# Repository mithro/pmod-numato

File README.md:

# pmod-numato

This adapter is useful for the following;

 * Adapting the "XADC" style to the "HS" style.
    - See [my high speed Pmod sheet for details](https://docs.google.com/spreadsheets/d/1D-GboyrP57VVpejQzEm0P1WEORo1LAIt92hk1bZGEoo/edit#gid=725118408).

 * From from Numato's spacing (0.3145 inch, pin to pin) to
   Digilent's spacing (0.3 inch, edge to edge).

The traces in a diff pair have been length and skewed matched with a tolerance
of ~1 mil.

The diff pairs as a group have been length matched to 0.8537 inches (21.6mm)
long with a tolerance of 20 mil (0.5mm).

To use Numato spacing device on Digilent host;
 * B side should be up.
 * The XHS side should be loaded with pins.
 * The XADC side should be loaded with socket.

To use Digilent spacing device on Numato host;
 * A side should be up.
 * The XHS side should be loaded with socket.
 * The XADC side should be loaded with pins.

# Board Manufacturing

 *  5mil (0.127mm) trace width
 *  5mil (0.127mm) trace clearance

 * 12 mil (0.3048mm) drill size
 *  6 mil (0.1524mm) annular ring
 * 24 mil (0.6096mm) via size (6mil+12mil+6mil)

 *  6 mil (0.1524) silkscreen width

This can be meet by;
 * [Hackvana by requesting the 5mil option](https://docs.google.com/document/d/1p6FH25ltGpzJQ5_8fbflDukqEKghiEcpuhJpngth2Is/edit)
 * [OHS Park's Four Layer Boards](http://docs.oshpark.com/services/)

## License

The board is licensed under a
Creative Commons Attribution-ShareAlike 4.0 International License.

You should have received a copy of the license along with this
work.  If not, see <http://creativecommons.org/licenses/by-sa/4.0/>.

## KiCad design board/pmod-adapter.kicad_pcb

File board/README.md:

5mil traces, 5mil clearance

0.8537 - length matched

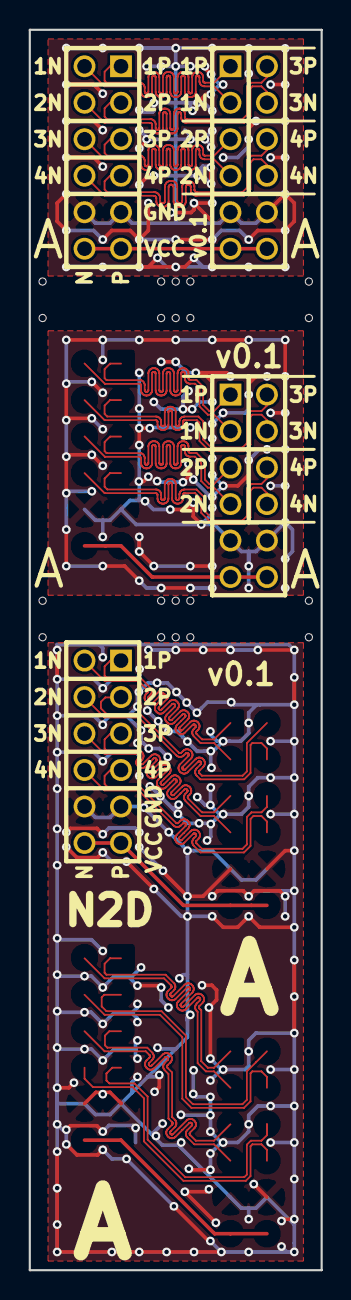
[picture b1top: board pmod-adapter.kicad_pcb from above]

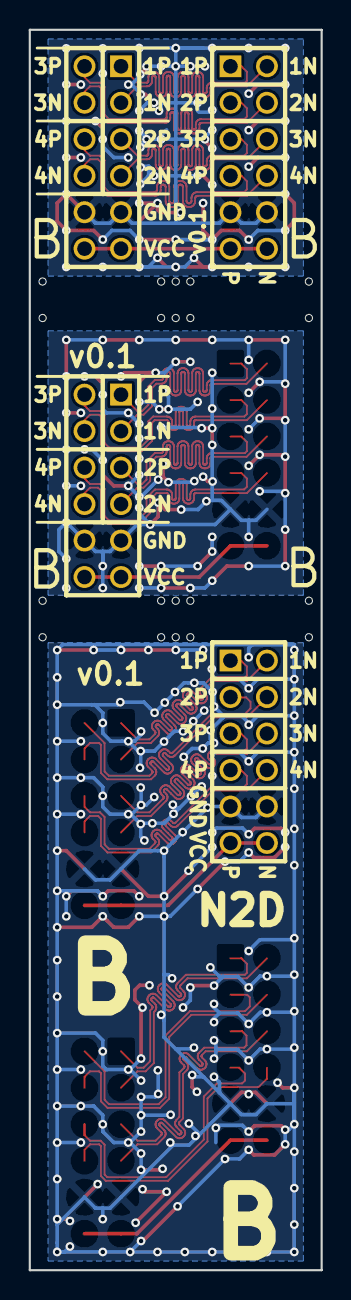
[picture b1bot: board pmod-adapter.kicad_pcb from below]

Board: 2 copper layers, 20.3 x 86.4 mm, 4 parts (2 on the bottom side), 13 nets.

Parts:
PH1, PH2: PMOD-Device-x2-Type-XHS; pmod_pin_array_6x2_hs
PX1, PX3: PMOD-Device-x2-Type-XADC; pmod_pin_array_6x2_xadc

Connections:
/GND2: PX1.5, PX1.11
/GND34: PH1.5, PH1.11, PH2.5, PH2.11, PX3.5, PX3.11
/J4A_N: PH1.2, PX3.7
/J4A_P: PH1.1, PX3.1
/J4B_N: PH1.8, PX3.8
/J4B_P: PH1.7, PX3.2
/J4C_N: PH1.4, PX3.9
/J4C_P: PH1.3, PX3.3
/J4D_N: PH1.10, PX3.10
/J4D_P: PH1.9, PX3.4
/VCC2: PX1.6, PX1.12
/VCC3: PH2.6, PH2.12
/VCC4: PH1.6, PH1.12, PX3.6, PX3.12

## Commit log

2016-11-15 Start.
2016-11-15 Adding LICENSE info.
2016-11-15 Adding another dimension.
2016-11-15 Changing the README a little.
2016-11-15 Increasing to 4 headers.
2016-11-19 Split the GND net for each part.
2016-11-19 Updating PCB.
2016-11-19 Lots of updates.
2016-11-19 Small updates.
2016-11-19 Working on getting the Numato spacing right.
2016-11-19 Updating comments a little.
2016-11-20 Rework the schematic to make board easier to route.
2016-11-20 Adding length matching scripts.
2016-11-20 Routing all pairs.
2016-11-20 Committing before doing length tunning.
2016-11-20 Length matching.
2016-11-20 Adding tie vias
2016-11-20 Adding board details.
2016-11-20 Working on the cuts and pours.
2016-11-20 Remove extra silkscreen object.
2016-11-26 Adding more gnd vias
2016-11-26 Temp commit.
2016-11-26 Slowly adding more vias.
2016-11-26 Fixes.
2016-11-26 One more via.
2016-11-26 Adding release scripts.
2016-11-26 Move the text around slightly.
2016-11-26 Slight silkscreen fixes.
2016-11-26 Making the text thicker.
2016-11-26 Small alignment fix.
2016-11-26 Fixing the B on the silkscreen.
2016-11-27 Fixing small variance.
2016-11-27 Fixing the diffpair documentation.
2016-11-27 Bumping version to v0.1
2016-11-27 Updating length matching script.
